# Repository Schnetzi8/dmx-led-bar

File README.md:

# dmx-led-bar
A dmx controllable strip of LEDs. With Web Interface for configuration.

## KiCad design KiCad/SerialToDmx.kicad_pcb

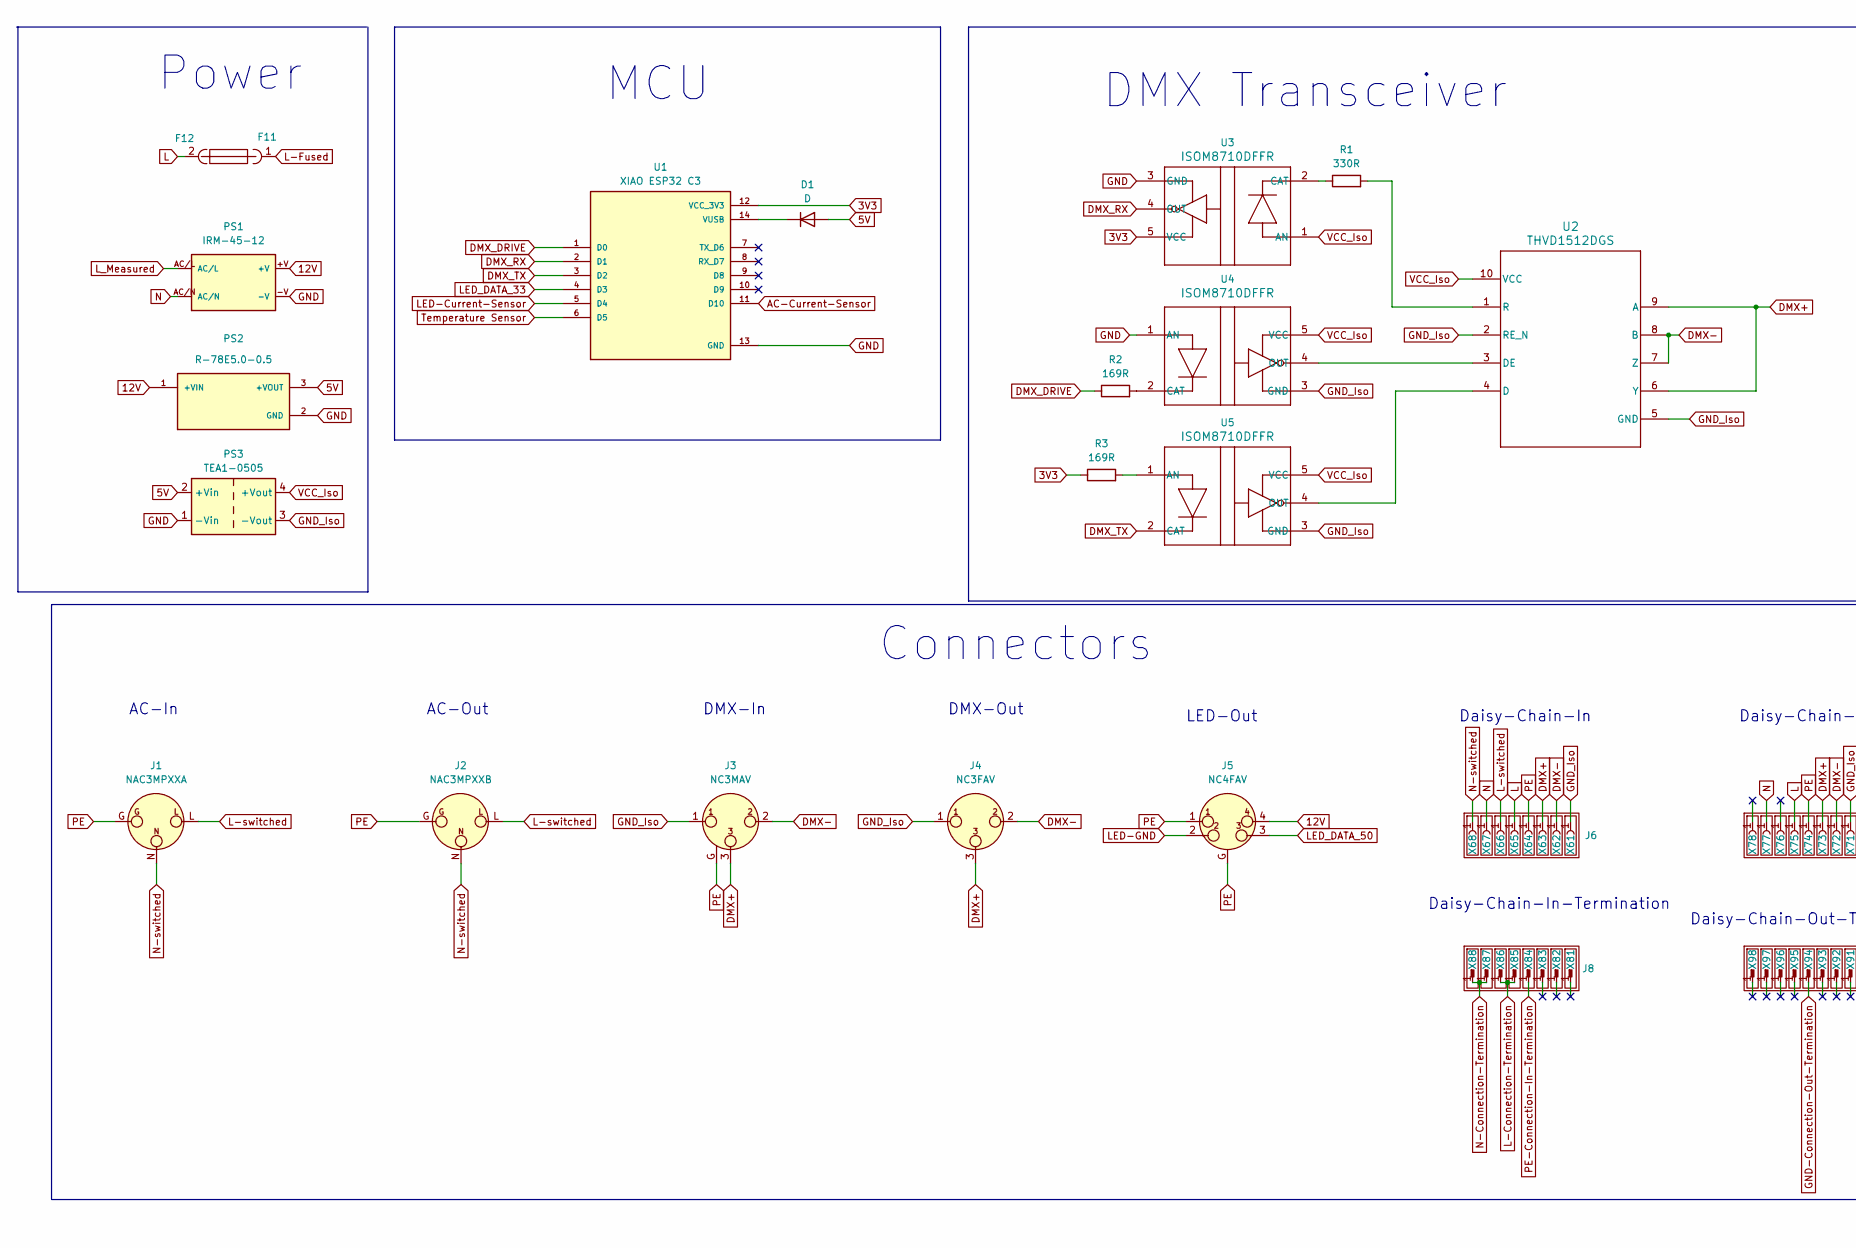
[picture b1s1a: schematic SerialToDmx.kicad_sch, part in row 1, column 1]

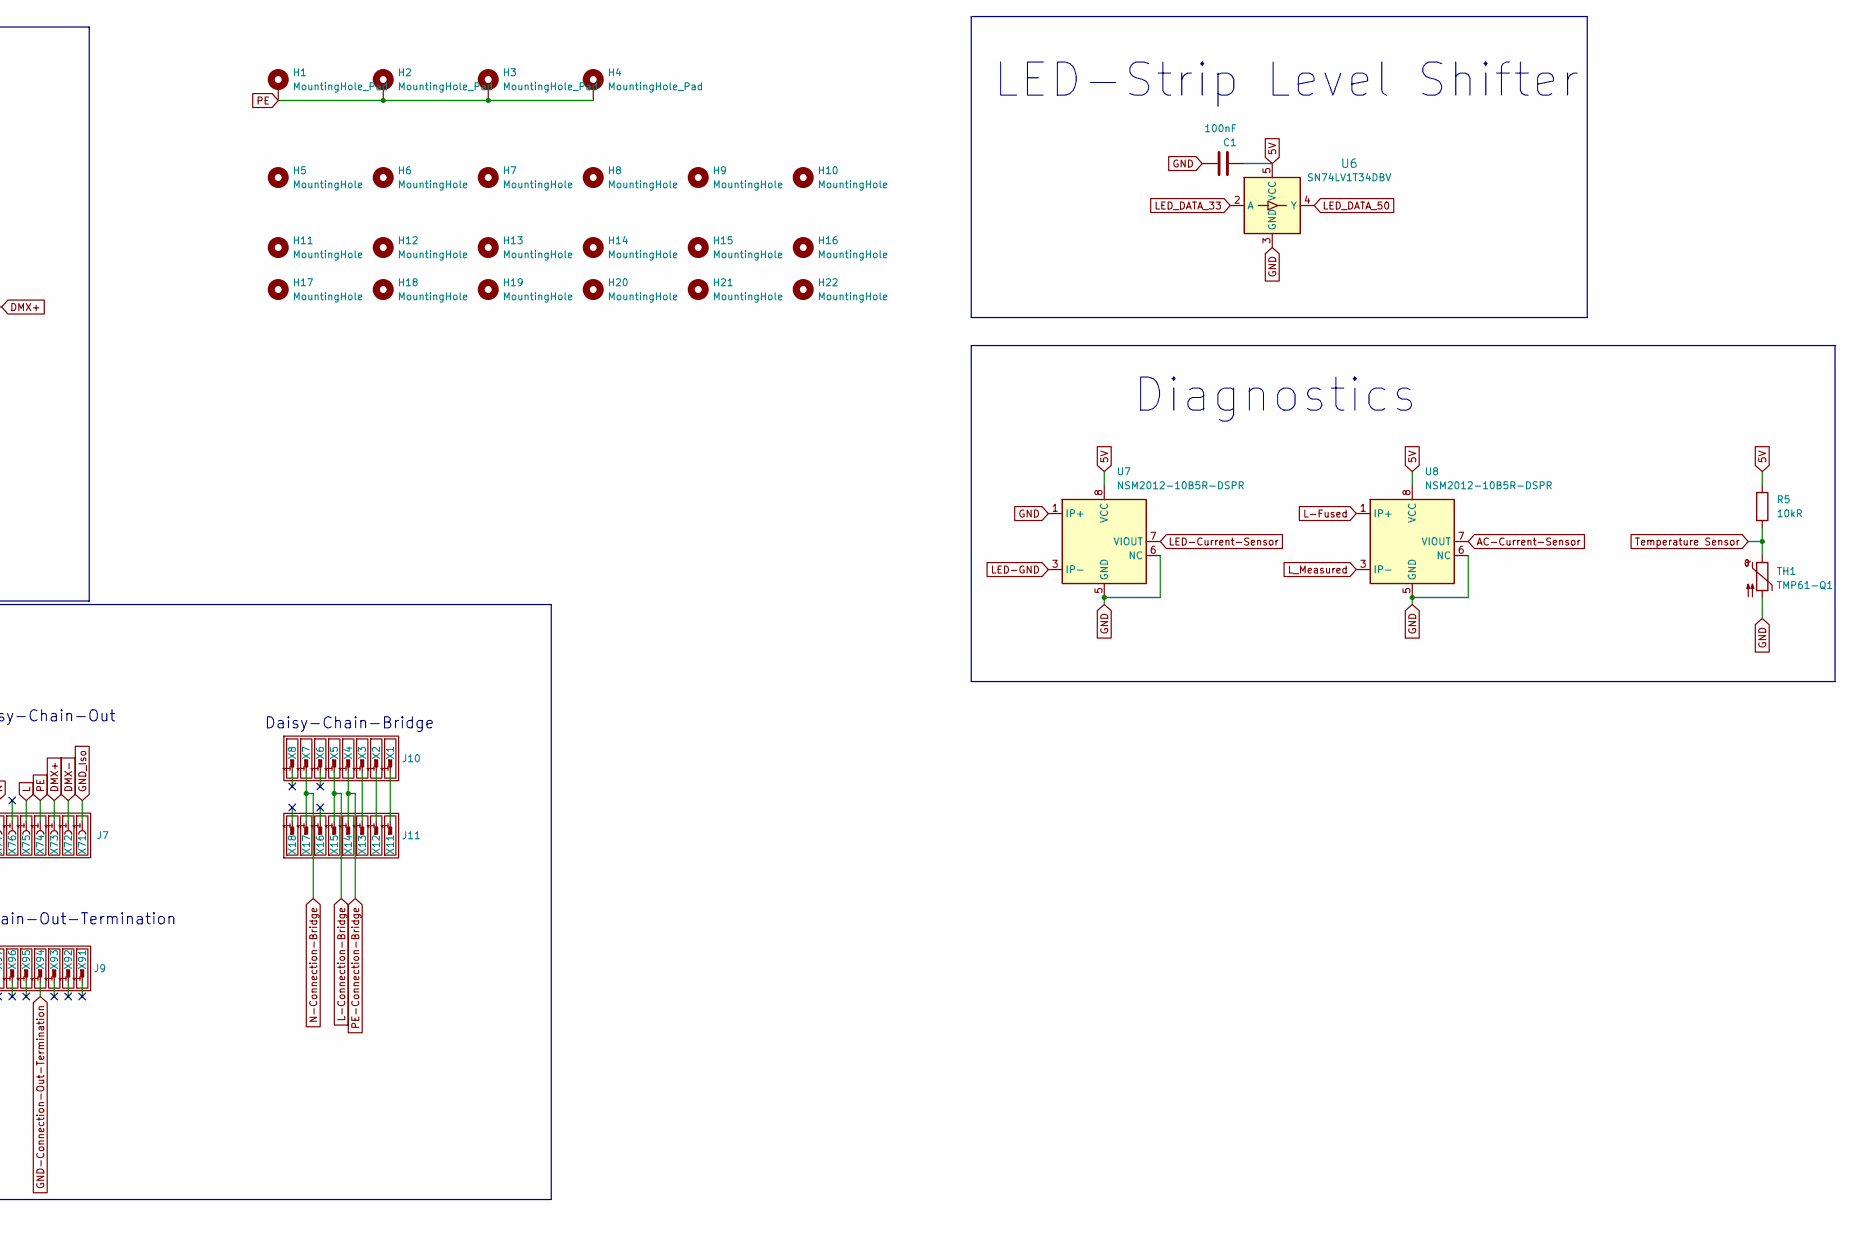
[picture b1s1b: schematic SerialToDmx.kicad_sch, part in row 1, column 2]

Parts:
C1: 100nF; C_0402_1005Metric_Pad0.74x0.62mm_HandSolder
D1: D; R_0402_1005Metric
F11: 01110501Z; fuseholder_111_501_Part1
F12: 01110501Z; fuseholder_111_501_Part2
H1, H2, H3, H4: MountingHole_Pad; MountingHole_3.2mm_M3_DIN965_Pad
H5, H6, H7, H8, H9, H10: MountingHole; MountingHole_3.2mm_M3
H11, H12, H13, H14, H15, H16, H17, H18, H19, H20, H21, H22: MountingHole; mouse-bite-2mm-slot
J1: NAC3MPXXA; DigiKey_Part_Number 708-1341-ND
J2: NAC3MPXXB; PARTREV N/A
J3: NC3MAV
J4: NC3FAV
J5: NC4FAV
J6, J7: Faston_01x08_socket
J8, J9, J10, J11: Faston_01x08_pin
PS1: IRM-45-12; CONV_IRM-45-12; PARTREV NA
PS2: R-78E5.0-0.5; CONV_R-78E5.0-0.5; PARTREV 4
PS3: TEA1-0505; Converter_DCDC_TRACO_TEA1-xxxx_THT
R1: 330R; R_0402_1005Metric
R2, R3: 169R; R_0402_1005Metric
R5: 10kR; R_0402_1005Metric
TH1: TMP61-Q1; R_0402_1005Metric
U1: XIAO ESP32 C3; XIAO-Generic-Thruhole-14P-2.54-21X17.8MM; PARTREV 23/05/2022
U2: THVD1512DGS; DGS0010A_N
U3, U4, U5: ISOM8710DFFR; ISOM8710; PARTREV 6
U6: SN74LV1T34DBV; SOT-23-5
U7, U8: NSM2012-10B5R-DSPR; SOIC-8_3.9x4.9mm_P1.27mm
X1, X2, X3, X4, X5, X6, X7, X8, X11, X12, X13, X14, X15, X16, X17, X18, X81, X82, X83, X84, X85, X86, X87, X88, X91, X92, X93, X94, X95, X96, X97, X98: 1217861-1; Faston_01x01_pin
X61, X62, X63, X64, X65, X66, X67, X68, X71, X72, X73, X74, X75, X76, X77, X78: 63994-1; Faston_01x01_socket

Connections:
3V3: R3.1, U1.12 (VCC_3V3), U3.5 (VCC)
5V: C1.2, D1.2 (A), PS2.3 (+VOUT), PS3.2 (+Vin), R5.1, U6.5 (VCC), U7.8 (VCC), U8.8 (VCC)
12V: J5.4, PS1.+V, PS2.1 (+VIN)
AC-Current-Sensor: U1.11 (D10), U8.7 (VIOUT)
DMX+: J3.3, J4.3, U2.6 (Y), U2.9 (A), X63.1, X73.1
DMX-: J3.2, J4.2, U2.7 (Z), U2.8 (B), X62.1, X72.1
DMX_DRIVE: R2.1, U1.1 (D0)
DMX_RX: U1.2 (D1), U3.4 (OUT)
DMX_TX: U1.3 (D2), U5.2 (CAT)
GND: C1.1, PS1.-V, PS2.2 (GND), PS3.1 (-Vin), TH1.2, U1.13 (GND), U3.3 (GND), U4.1 (AN), U6.3 (GND), U7.1 (IP+), U7.2 (IP+), U7.5 (GND), U7.6 (NC), U8.5 (GND), U8.6 (NC)
GND-Connection-Out-Termination: X94.1
GND_Iso: J3.1, J4.1, PS3.3 (-Vout), U2.2 (RE_N), U2.5 (GND), U4.3 (GND), U5.3 (GND), X61.1, X71.1
L: F12.2, X65.1, X75.1
L-Connection-Bridge: X5.1, X15.1
L-Connection-Termination: X85.1, X86.1
L-Fused: F11.1, U8.1 (IP+), U8.2 (IP+)
L-switched: J1.L, J2.L, X66.1
LED-Current-Sensor: U1.5 (D4), U7.7 (VIOUT)
LED-GND: J5.2, U7.3 (IP-), U7.4 (IP-)
LED_DATA_33: U1.4 (D3), U6.2 (A)
LED_DATA_50: J5.3, U6.4 (Y)
L_Measured: PS1.AC/L, U8.3 (IP-), U8.4 (IP-)
N: PS1.AC/N, X67.1, X77.1
N-Connection-Bridge: X7.1, X17.1
N-Connection-Termination: X87.1, X88.1
N-switched: J1.N, J2.N, X68.1
unnamed: D1.1 (K), U1.14 (VUSB)
unnamed: U2.4 (D), U5.4 (OUT)
unnamed: U2.3 (DE), U4.4 (OUT)
unnamed: R1.2, U2.1 (R)
unnamed: R1.1, U3.2 (CAT)
unnamed: R2.2, U4.2 (CAT)
unnamed: R3.2, U5.1 (AN)
unnamed: X1.1, X11.1
unnamed: X2.1, X12.1
unnamed: X3.1, X13.1
PE: H1.1, H2.1, H3.1, H4.1, J1.G, J2.G, J3.G, J5.1, J5.G, X64.1, X74.1
PE-Connection-Bridge: X4.1, X14.1
PE-Connection-In-Termination: X84.1
Temperature Sensor: R5.2, TH1.1, U1.6 (D5)
VCC_Iso: PS3.4 (+Vout), U2.10 (VCC), U3.1 (AN), U4.5 (VCC), U5.5 (VCC)

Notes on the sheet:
LED-Out
Daisy-Chain-In-Termination
Diagnostics
AC-In
Daisy-Chain-Out-Termination
DMX Transceiver
DMX-Out
MCU
Daisy-Chain-Out
Daisy-Chain-Bridge
LED-Strip Level Shifter
Power
Daisy-Chain-In
DMX-In
Connectors
AC-Out

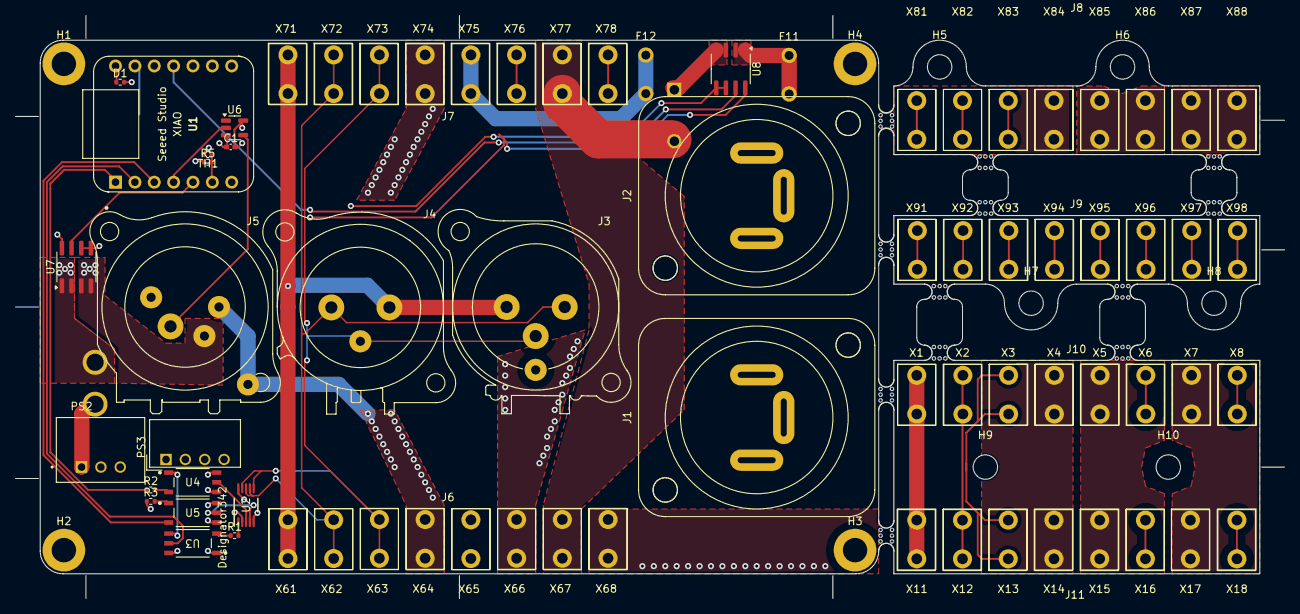
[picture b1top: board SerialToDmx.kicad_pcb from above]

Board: 4 copper layers, 166.5 x 76.5 mm, 101 parts (1 on the bottom side), 39 nets.

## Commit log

2024-07-25 Added Manual
2024-07-30 Started Work on Conn Box V2
2024-07-30 Removed last backup
2024-07-30 Moved ReadMe to correct Location
2024-07-31 Started on Mounting Holes for Terminators and Bridge
2024-07-31 Improved Layout for Case
2024-08-13 Adjusted Board for new Case
2024-08-13 Revert "Adjusted Board for new Case"
    This reverts commit 228f85c15c617e8d061b070415350dd353ddd87a.
2024-08-13 With Files
2024-08-14 Switched Female and Male XLR 3-Pin Connectors
